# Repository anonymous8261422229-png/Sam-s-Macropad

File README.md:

hello every one hope you enjoy building this project this project uses Seeed XIAO RP2040 as microcontroller four MX-Style switches and SK6812 MINI-E LEDs for RGB and M3x16mm screws for holding the model together 
first we we start by making a schematic like this one below 
after that we rearrange the parts like this one below and also place them in rectangle i am also providing the dimensions in the images

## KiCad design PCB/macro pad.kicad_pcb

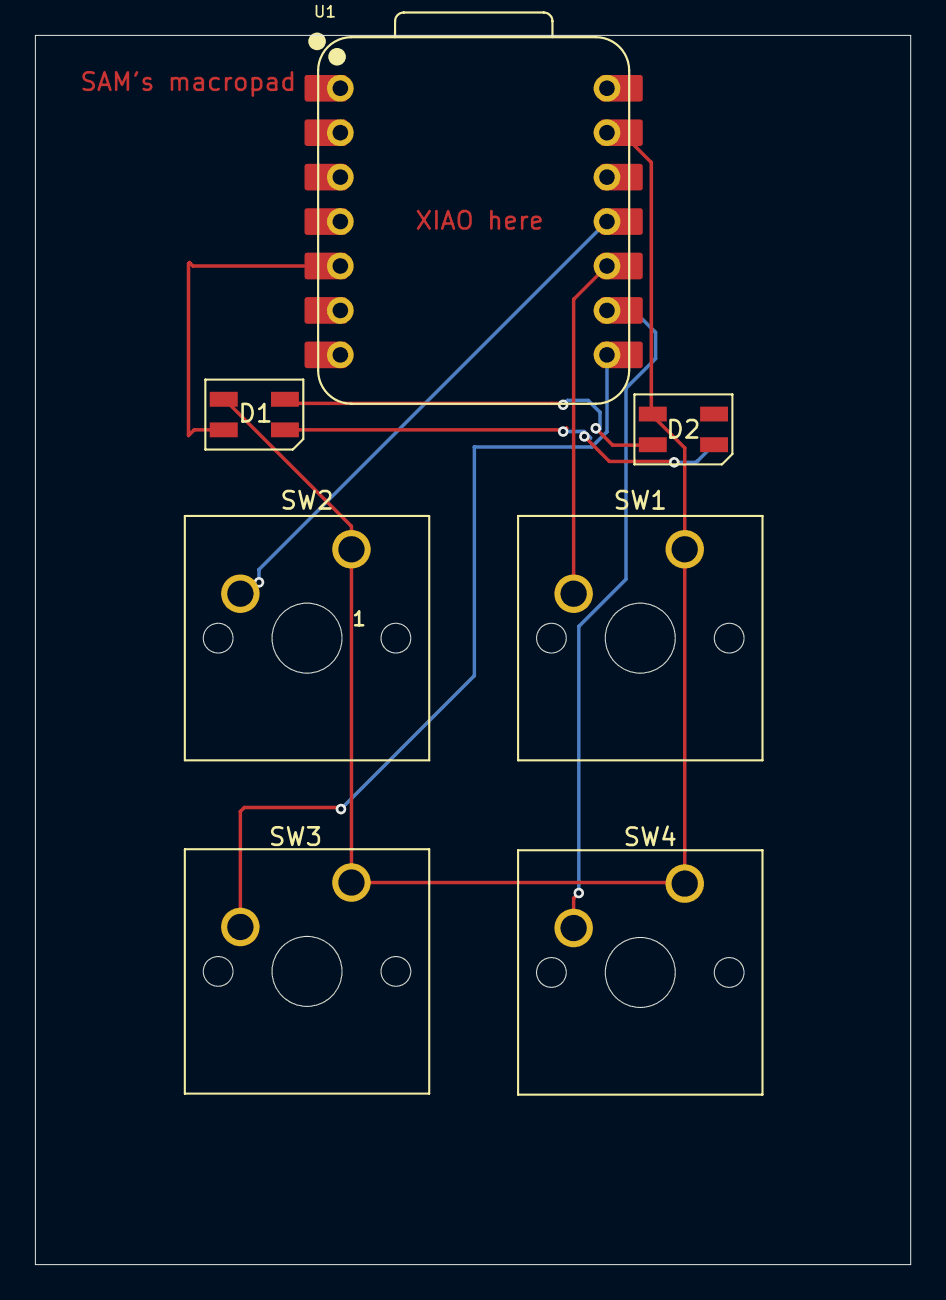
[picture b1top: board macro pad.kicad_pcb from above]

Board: 2 copper layers, 50.0 x 70.3 mm, 7 parts (0 on the bottom side), 8 nets.

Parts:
D1, D2: SK6812MINI; LED_SK6812MINI_PLCC4_3.5x3.5mm_P1.75mm
SW1, SW2, SW3, SW4: SW_Push; SW_Cherry_MX_1.00u_PCB
U1: XIAO-RP2040-DIP

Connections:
GND: D1.1 (DOUT), D2.1 (DOUT), SW1.1, SW2.1, SW3.1, SW4.1, U1.13 (GND)
unnamed: D1.3 (DIN), D2.3 (DIN)
unnamed: D1.4 (VDD), D2.2 (VSS)
unnamed: D1.2 (VSS), U1.5 (GPIO6/SDA)
unnamed: SW4.2, U1.8 (GPIO1/RX)
unnamed: SW3.2, U1.9 (GPIO2/SCK)
unnamed: SW2.2, U1.11 (GPIO3/MOSI)
unnamed: SW1.2, U1.10 (GPIO4/MISO)

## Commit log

2026-01-21 Add files via upload
    the base CAD and the top plate
2026-01-21 README.md
    check this out !!!
